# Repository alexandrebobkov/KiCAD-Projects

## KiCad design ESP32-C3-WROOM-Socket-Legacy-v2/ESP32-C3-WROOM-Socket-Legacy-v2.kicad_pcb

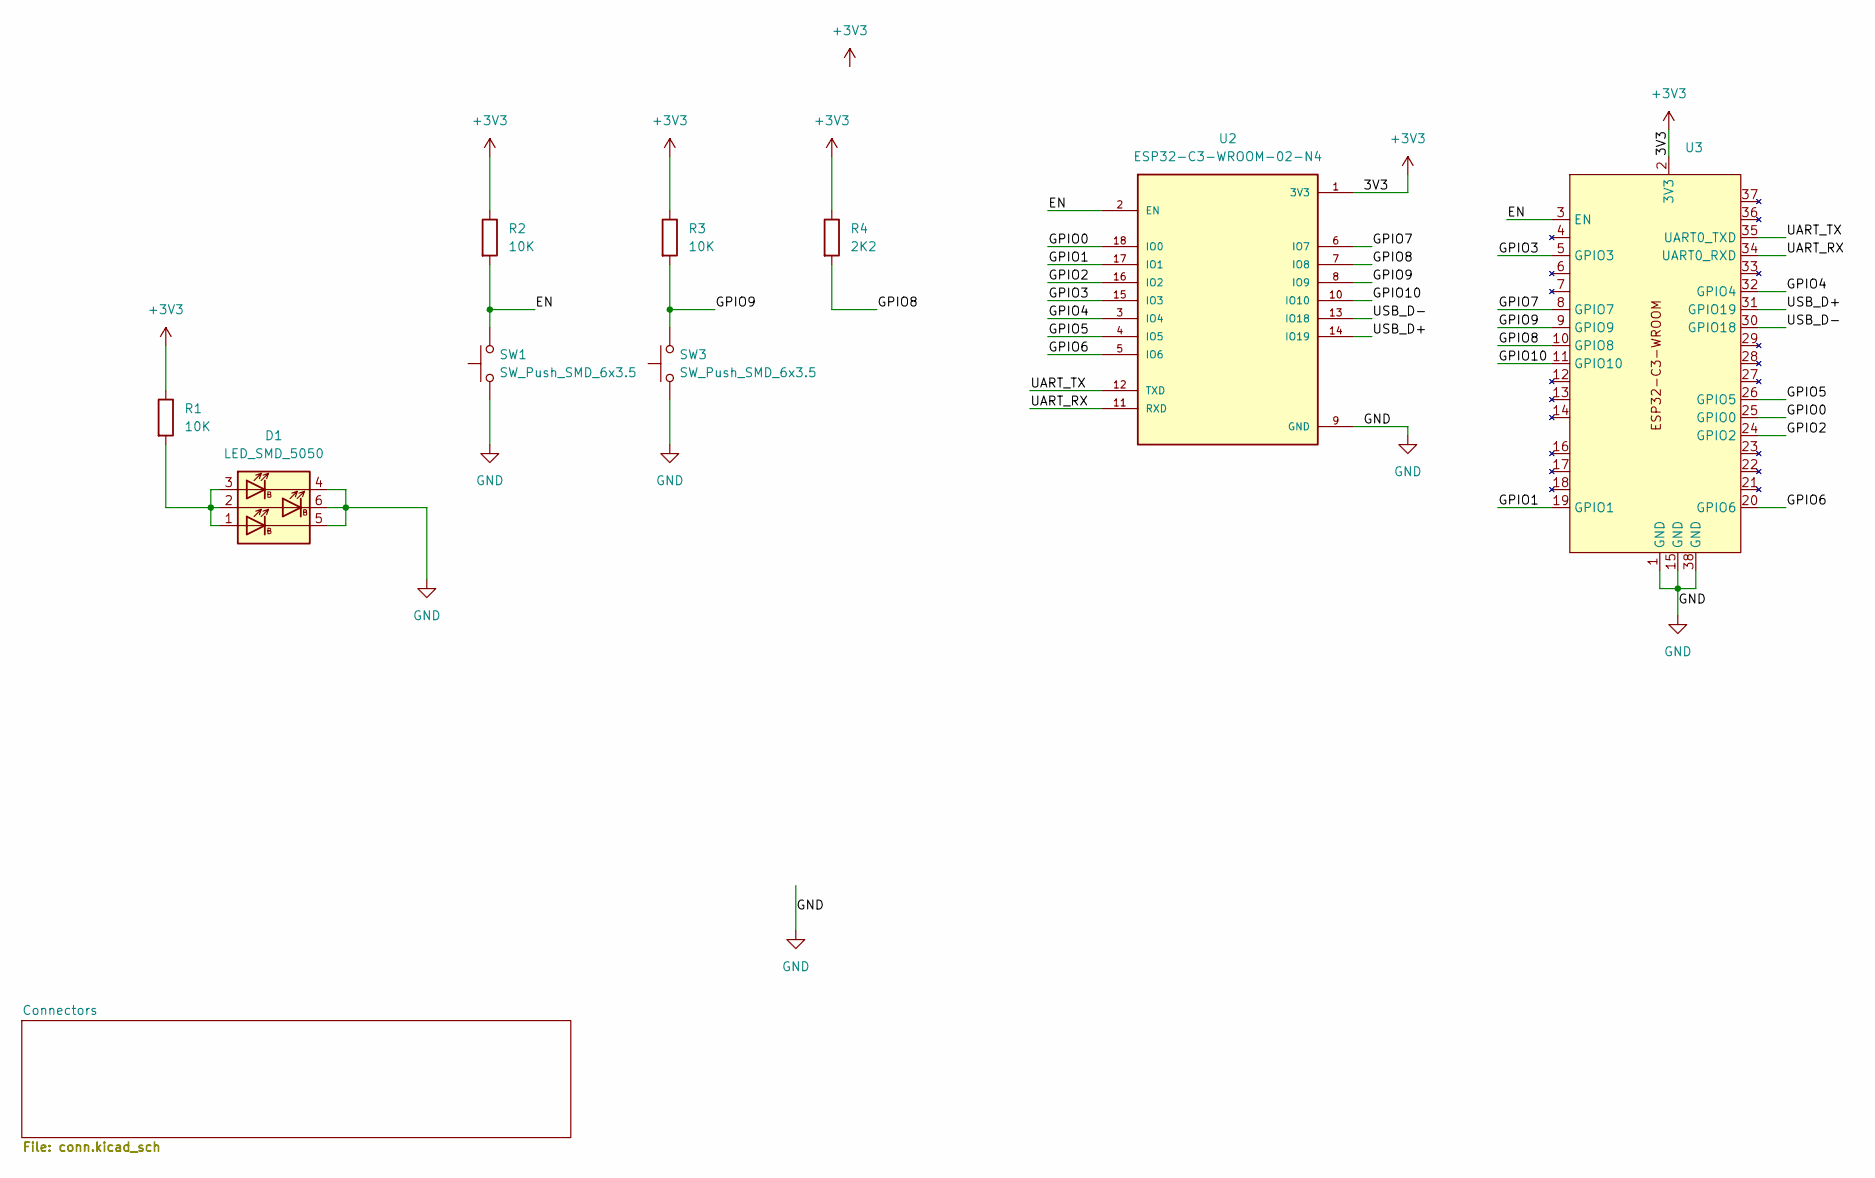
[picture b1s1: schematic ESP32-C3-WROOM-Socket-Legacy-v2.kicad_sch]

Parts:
D1: LED_SMD_5050; LED_5050-6
R1, R2, R3: 10K; R_1206_3216Metric_Pad1.30x1.75mm_HandSolder
R4: 2K2; R_1206_3216Metric_Pad1.30x1.75mm_HandSolder
SW1, SW3: SW_Push_SMD_6x3.5; SW_PUSH_6x3.5mm
U2: ESP32-C3-WROOM-02-N4; ESP32-C3-WROOM-02-H4
U3: CONN-ESP32-WROOM-Adapter-Legacy-v3

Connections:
+3V3: R1.1, R2.1, R3.1, R4.1, U2.1 (3V3), U3.2 (3V3)
/EN: R2.2, SW1.2, U2.2 (EN), U3.3 (EN)
/GPIO0: U2.18 (IO0), U3.25 (GPIO0)
/GPIO1: U2.17 (IO1), U3.19 (GPIO1)
/GPIO2: U2.16 (IO2), U3.24 (GPIO2)
/GPIO3: U2.15 (IO3), U3.5 (GPIO3)
/GPIO4: U2.3 (IO4), U3.32 (GPIO4)
/GPIO5: U2.4 (IO5), U3.26 (GPIO5)
/GPIO6: U2.5 (IO6), U3.20 (GPIO6)
/GPIO7: U2.6 (IO7), U3.8 (GPIO7)
/GPIO8: R4.2, U2.7 (IO8), U3.10 (GPIO8)
/GPIO9: R3.2, SW3.2, U2.8 (IO9), U3.9 (GPIO9)
/GPIO10: U2.10 (IO10), U3.11 (GPIO10)
/UART_RX: U2.11 (RXD), U3.34 (UART0_RXD)
/UART_TX: U2.12 (TXD), U3.35 (UART0_TXD)
/USB_D+: U2.14 (IO19), U3.31 (GPIO19)
/USB_D-: U2.13 (IO18), U3.30 (GPIO18)
GND: D1.4 (KR), D1.5 (AG), D1.6 (KR), SW1.1, SW3.1, U2.9 (GND), U2.19 (GND__1), U2.20 (GND__2), U2.21 (GND__3), U2.22 (GND__4), U2.23 (GND__5), U2.24 (GND__6), U2.25 (GND__7), U2.26 (GND__8), U2.27 (GND__9), U2.28 (GND__10), U2.29 (GND__11), U2.30 (GND__12), U2.31 (GND__13), U2.32 (GND__14), U2.33 (GND__15), U2.34 (GND__16), U2.35 (GND__17), U2.36 (GND__18), U2.37 (GND__19), U2.38 (GND__20), U2.39 (GND__21), U3.1 (GND), U3.15 (GND), U3.38 (GND)
unnamed: D1.1 (AB), D1.2 (KB), D1.3 (AR), R1.2

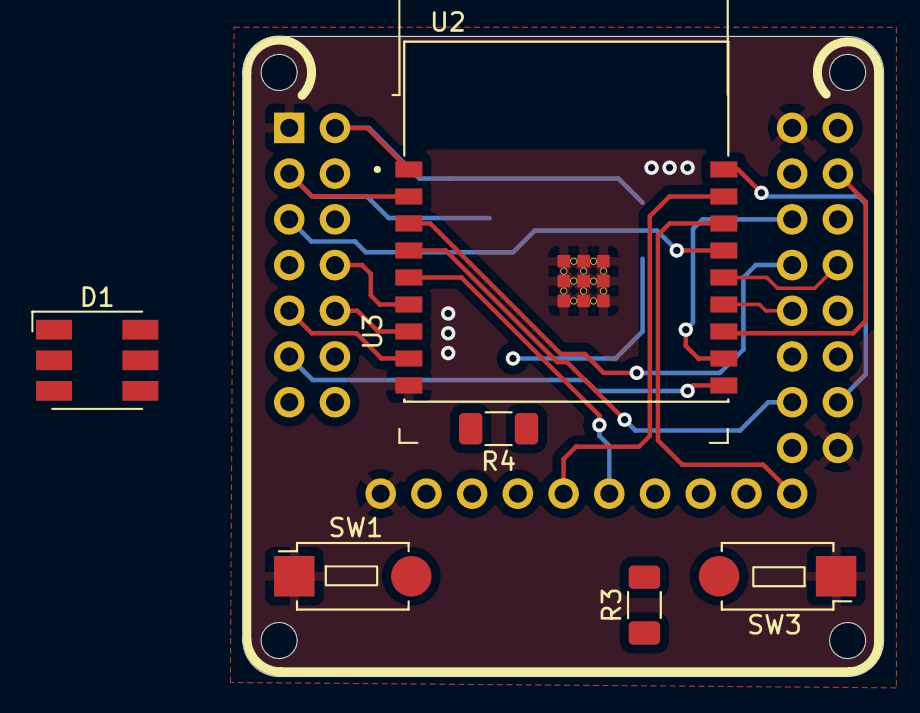
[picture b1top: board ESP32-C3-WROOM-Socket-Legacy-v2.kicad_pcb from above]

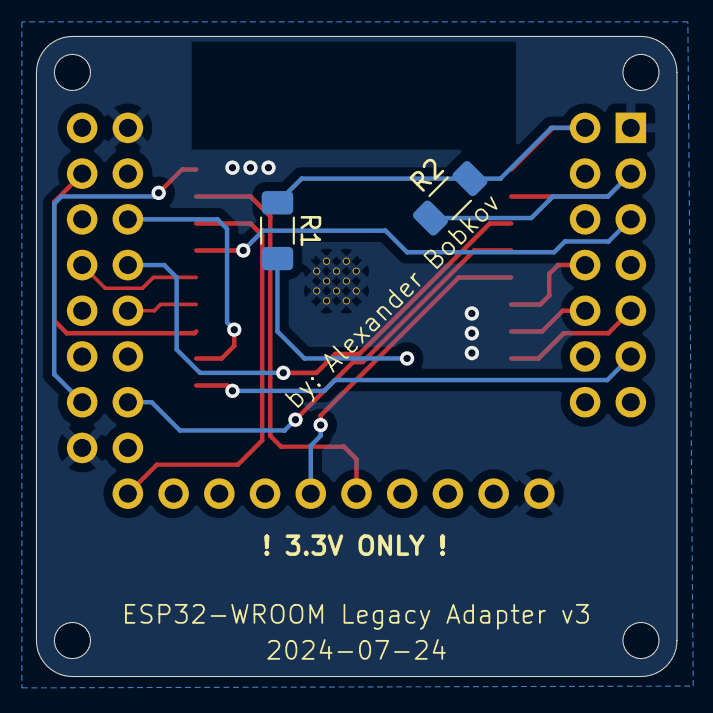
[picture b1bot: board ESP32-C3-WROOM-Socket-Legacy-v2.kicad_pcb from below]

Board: 2 copper layers, 35.6 x 35.6 mm, 9 parts (2 on the bottom side), 19 nets.

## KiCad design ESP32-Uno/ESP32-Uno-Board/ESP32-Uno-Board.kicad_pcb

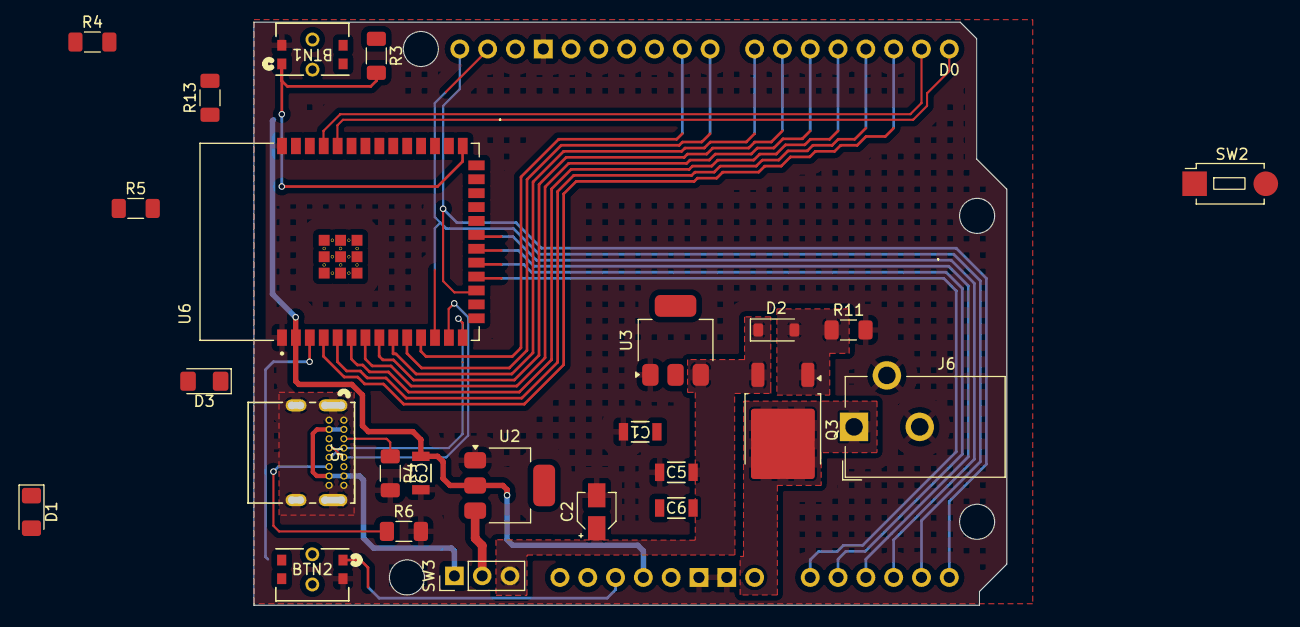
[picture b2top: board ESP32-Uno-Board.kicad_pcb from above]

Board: 2 copper layers, 68.8 x 53.2 mm, 27 parts (0 on the bottom side), 15 nets.

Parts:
A1: Arduino_Uno_WiFi_R2_Shield; Arduino Uno
BTN1, BTN2: SW_Push_SMD_6x3.5; Button-Tacktile-TL1014BF160
C1, C5, C9: 1uF; CAP_CL31_SAM
C2: 1000uF; CP_Elec_3x5.3
C6: 10uF; CAP_CL31_SAM
D1, D3: LED; LED_1206_3216Metric_Pad1.42x1.75mm_HandSolder
D2: MMSZ52XXB; D_SOD-123
H1: MountingHole; Arduino Uno
J5: USB-C_Receptacle_Data_16P_GCT-USB4085; USB-C_GCT CONN16_USB4085-GF-A
J6: Barrel_Jack_Switch; BarrelJack_CUI_PJ-102AH_Horizontal
Q3: DMP6180SK3; TO-252-2
R3, R4#2, R11, R13: 10k; R_1206_3216Metric_Pad1.30x1.75mm_HandSolder
R4, R6: 5K1; R_1206_3216Metric_Pad1.30x1.75mm_HandSolder
R5: 2K2; R_1206_3216Metric_Pad1.30x1.75mm_HandSolder
SW2: SW_Push_SMD_6x3.5; SW_PUSH_6x3.5mm
SW3: SW_SPDT; PinHeader_1x03_P2.54mm_Vertical
U2: LM1117MP-3.3; SOT-223
U3: AMS1117-5V; SOT-223
U6: ESP32-S3-WROOM-1; ESP32-S3-WROOM-2-N32R8V

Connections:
+3V3: A1.3V3 (3.3V), C9.1, D3.2 (A), R3.1, R4#2.1, R5.1, R13.1, U2.2 (VO), U6.2 (3V3)
+5V: A1.5V1 (5V), C1.1, U2.3 (VI), U3.2 (VO)
/CC1: J5.A5 (CC1), R4.1
/CC2: J5.B5 (CC2), R6.1
/G: D2.2 (A), Q3.1 (G), R11.1
/GPIO0: BTN1.1, R3.2, U6.27 (IO0)
/GPIO46: SW2.1, U6.16 (IO46)
/USB_D+: J5.A6 (D+), J5.B6 (D+), U6.14 (IO20)
/USB_D-: J5.A7 (D-), J5.B7 (D-), U6.13 (IO19)
/VIN: C2.1, C5.2, C6.1, D2.1 (K), Q3.3 (S), SW3.3 (C)
/VUSB: D1.2 (A), J5.A4 (VBUS), J5.A9 (VBUS), J5.B4 (VBUS), J5.B9 (VBUS), SW3.1 (A)
/~RESET: BTN2.1, R13.2, U6.3 (EN)
GND: A1.GND1 (GND), A1.GND2 (GND), A1.GND3 (GND), BTN1.2, BTN2.2, C1.2, C2.2, C5.1, C6.2, C9.2, J5.A1 (GND), J5.A12 (GND), J5.B1 (GND), J5.B12 (GND), J5.S1 (SHIELD), J5.S2 (SHIELD), J5.S3 (SHIELD), J5.S4 (SHIELD), J6.2, J6.3, R4.2, R6.2, R11.2, SW2.2, U2.1 (GND), U3.1 (ADJ), U6.1 (GND), U6.40 (GND)
PWR: J6.1, Q3.2 (D)
VCC: SW3.2 (B), U3.3 (VI)

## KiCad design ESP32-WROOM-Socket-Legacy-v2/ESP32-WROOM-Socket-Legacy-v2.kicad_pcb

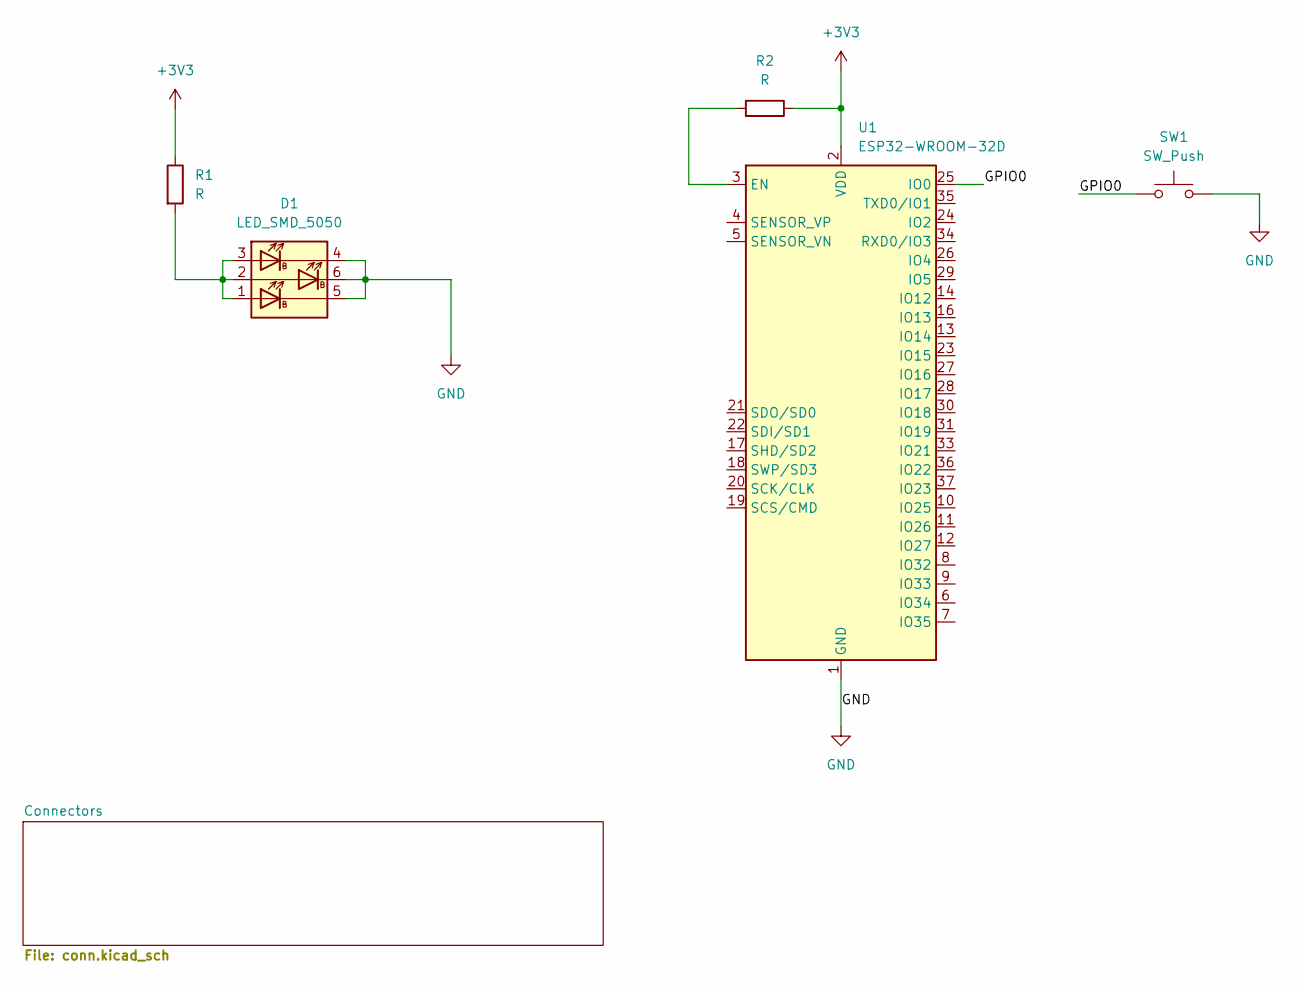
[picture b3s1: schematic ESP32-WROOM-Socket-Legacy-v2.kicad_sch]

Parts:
D1: LED_SMD_5050; LED_5050-6
R1, R2: R; R_1206_3216Metric_Pad1.30x1.75mm_HandSolder
SW1: SW_Push; SW_SPST_6x3
U1: ESP32-WROOM-32D; ESP32-WROOM-Adapter-Legacy-v3

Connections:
+3V3: R1.1, R2.1, U1.2 (VDD)
/GPIO0: SW1.1, U1.25 (IO0)
GND: D1.4 (KR), D1.5 (AG), D1.6 (KR), SW1.2, U1.1 (GND), U1.15 (GND), U1.38 (GND), U1.39 (GND)
unnamed: D1.1 (AB), D1.2 (KB), D1.3 (AR), R1.2
unnamed: R2.2, U1.3 (EN)

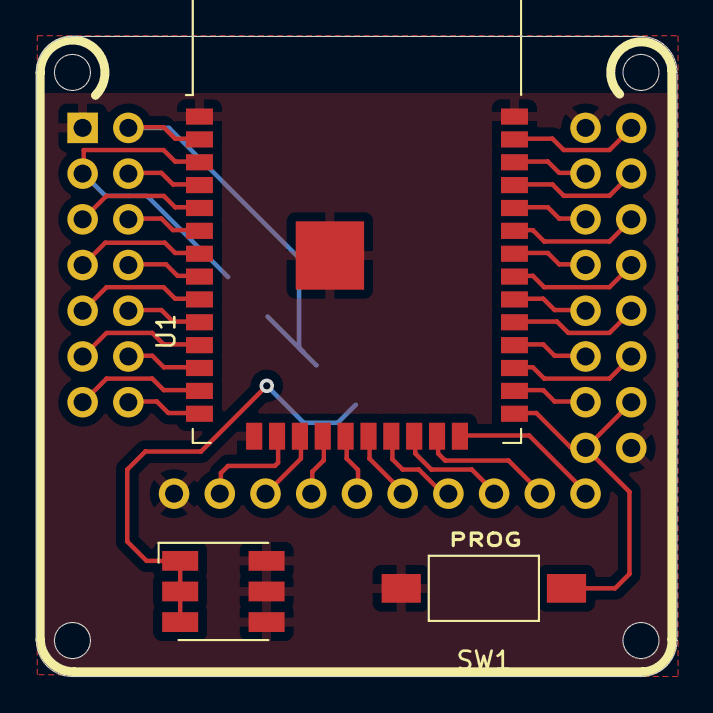
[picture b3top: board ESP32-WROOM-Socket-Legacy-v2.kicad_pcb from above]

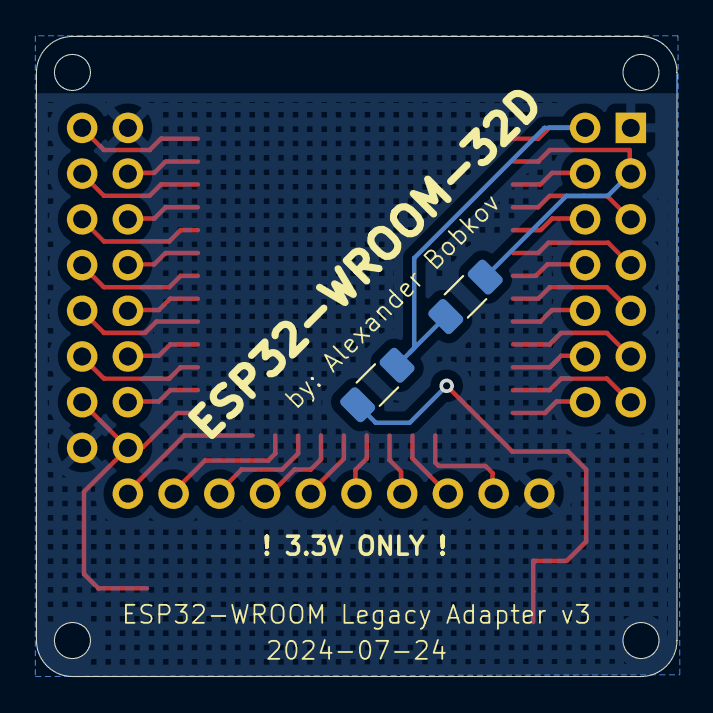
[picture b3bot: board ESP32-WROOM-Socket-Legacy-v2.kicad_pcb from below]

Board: 2 copper layers, 35.6 x 35.6 mm, 5 parts (2 on the bottom side), 5 nets.

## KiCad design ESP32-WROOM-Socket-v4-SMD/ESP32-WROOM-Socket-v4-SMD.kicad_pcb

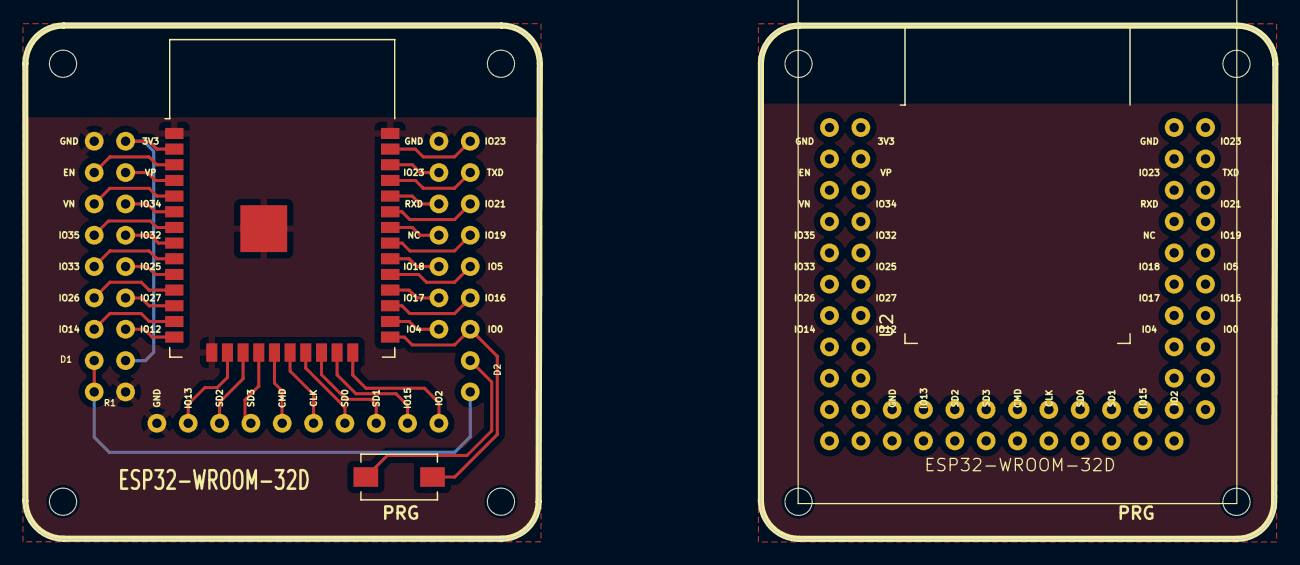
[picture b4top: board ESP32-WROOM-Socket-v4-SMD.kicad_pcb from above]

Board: 2 copper layers, 41.7 x 41.7 mm, 14 parts (0 on the bottom side), 6 nets.

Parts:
D1: PWR; LED_2.5mm
D2: PROG; LED_2.5mm
H1, H1#2, H2, H2#2, H3, H3#2, H4, H4#2: MountingHole_Pad_MP; MountingHole_2.2mm_M2
R1: R; R_2.5mm
SW1: PRG; SW_SPST_EVQPE1
U1: ESP32-WROOM-32D; ESP32-WROOM-Adapter-2
U2: ESP32-WROOM-32D; ESP32-WROOM-Adapter-Socket

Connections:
+3V3: D1.2 (A), U1.2 (VDD)
/PRG: SW1.1, U1.25 (IO0)
GND: R1.2, U1.1 (GND), U1.15 (GND), U1.38 (GND), U1.39 (GND)
unnamed: D1.1 (K), D2.1 (K), R1.1
unnamed: D2.2 (A), SW1.2
unnamed: U2.1 (GND), U2.38 (GND)

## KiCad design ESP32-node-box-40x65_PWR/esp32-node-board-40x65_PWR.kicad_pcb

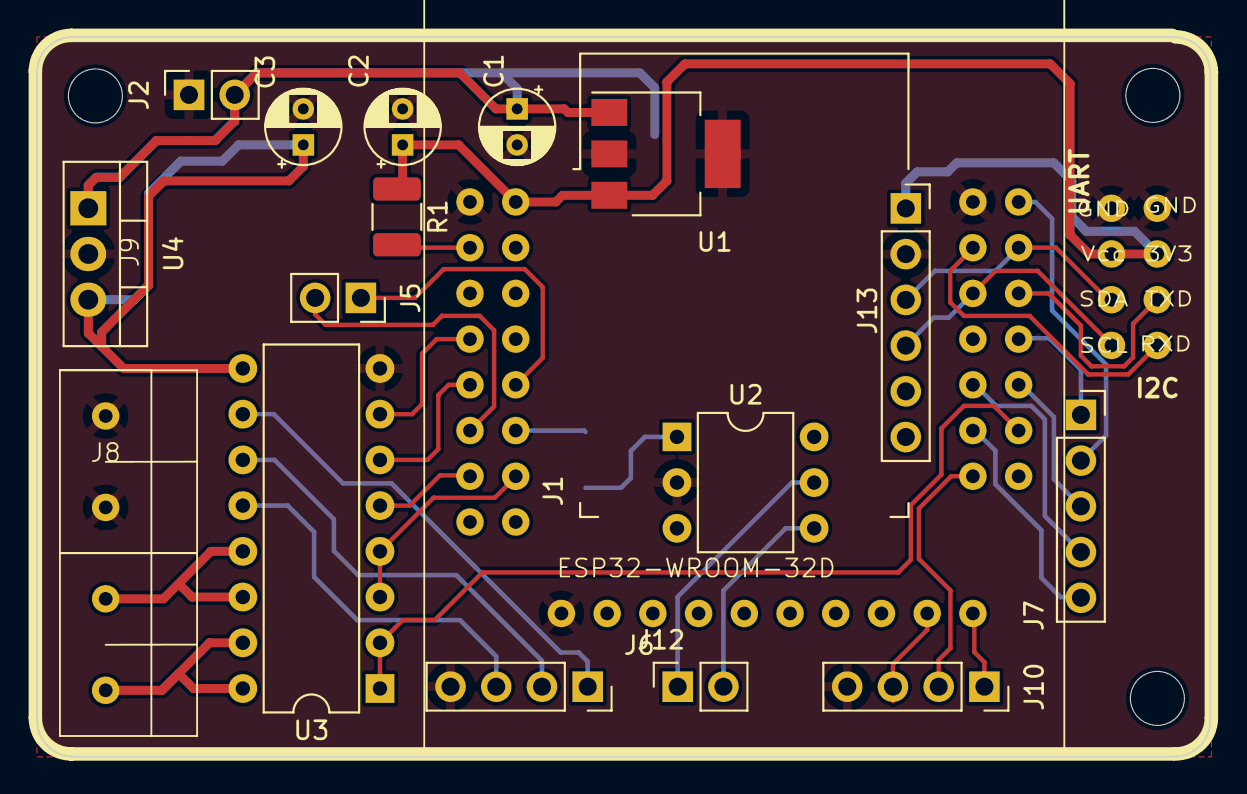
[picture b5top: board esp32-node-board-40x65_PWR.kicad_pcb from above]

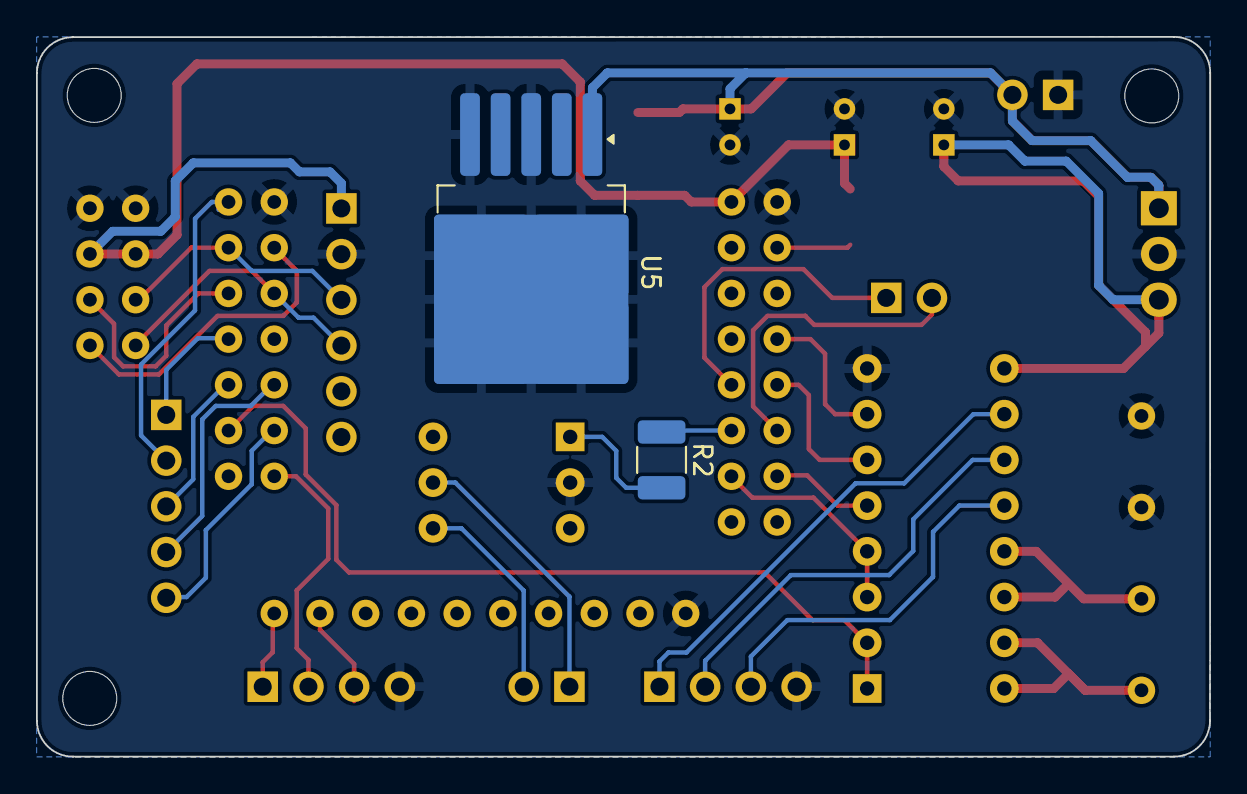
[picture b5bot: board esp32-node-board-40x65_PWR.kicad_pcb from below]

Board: 2 copper layers, 65.2 x 40.0 mm, 25 parts (2 on the bottom side), 33 nets.

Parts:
C1, C2, C3: 1uF; CP_Radial_D4.0mm_P2.00mm
H1, H2, H4: MountingHole_Pad; MountingHole_3mm
J1: ESP32-WROOM-Adapter-Socket-2
J2: PWD; PinSocket_1x02_P2.54mm_Vertical
J3: UART; Conn_UART
J4: I2C; Conn_I2C
J5: DAC_Socket; PinSocket_1x02_P2.54mm_Vertical
J6: SOURCE; PinSocket_1x04_P2.54mm_Vertical
J7: GPIO; PinSocket_1x05_P2.54mm_Vertical
J8, J9: Conn_01x02_Socket; Conn_Terminal_5mm
J10: ADC; PinSocket_1x04_P2.54mm_Vertical
J12: Conn_01x02_Socket; PinSocket_1x02_P2.54mm_Vertical
J13: Conn_01x06_Socket; PinSocket_1x06_P2.54mm_Vertical
R1: 10K; R_1210_3225Metric_Pad1.30x2.65mm_HandSolder
R2: 1K; R_1210_3225Metric_Pad1.30x2.65mm_HandSolder
U1: MAX1726EUK33; SOT-223-3_TabPin2
U2: 4N35; DIP-6_W7.62mm
U3: ULN2003; DIP-16_W7.62mm
U4: L7805; LD1117
U5: LM2596S-ADJ; TO-263-5_TabPin3

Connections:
+3V3: C2.1, J1.2 (VDD), J3.3V3, J4.Vcc (VCC), J13.1, R1.1, U1.3 (VO)
+5V: C3.1, U3.9 (COM), U4.3 (OUT)
/ADC2_CH0: J1.26 (IO4), J10.2
/ADC2_CH2: J1.24 (IO2), J10.1
/ADC2_CH3: J1.23 (IO15), J10.3
/DAC1: J1.10 (IO25), J5.1
/DAC2: J1.11 (IO26), J5.2
/EN: J1.3 (EN), R1.2
/GPIO5: J1.29 (IO5), J7.3
/GPIO17: J1.28 (IO17), J7.5
/GPIO18: J1.30 (IO18), J7.4
/GPIO19: J1.31 (IO19), J7.1
/GPIO23: J1.37 (IO23), J7.2
/GPIO27: J1.12 (IO27), R2.1
/OUT1: J1.27 (IO16), U3.1 (I1), U3.2 (I2)
/OUT2: J1.14 (IO12), U3.3 (I3), U3.4 (I4)
/OUT3: J1.13 (IO14), U3.5 (I5)
/OUT4: J1.9 (IO33), U3.6 (I6)
/OUT5: J1.7 (IO35), U3.7 (I7)
/RXD: J1.34 (RXD0), J3.RXD, J13.4
/SCL: J1.36 (SCL), J4.SCL
/SDA: J1.33 (SDA), J4.SDA
/SOURCE1: J8.2, U3.15 (O2), U3.16 (O1)
/SOURCE2: J8.1, U3.13 (O4), U3.14 (O3)
/SOURCE3: J6.3, U3.12 (O5)
/SOURCE4: J6.2, U3.11 (O6)
/SOURCE5: J6.1, U3.10 (O7)
/TXD: J1.35 (TXD0), J3.TXD, J13.3
/V1+: J12.1, U2.5
/V1-: J12.2, U2.4
/VDC: C1.1, J2.2, U1.1 (VI), U4.1 (IN), U5.1 (VIN)
GND: C1.2, C2.2, C3.2, J1.1 (GND), J1.15 (GND), J1.38 (GND), J2.1, J3.GND, J4.GND, J6.4, J9.1, J9.2, J10.4, J13.2, U1.2 (GND), U2.2, U3.8 (GND), U4.2 (GND), U5.3 (GND), U5.5 (~ON/OFF)
unnamed: R2.2, U2.1

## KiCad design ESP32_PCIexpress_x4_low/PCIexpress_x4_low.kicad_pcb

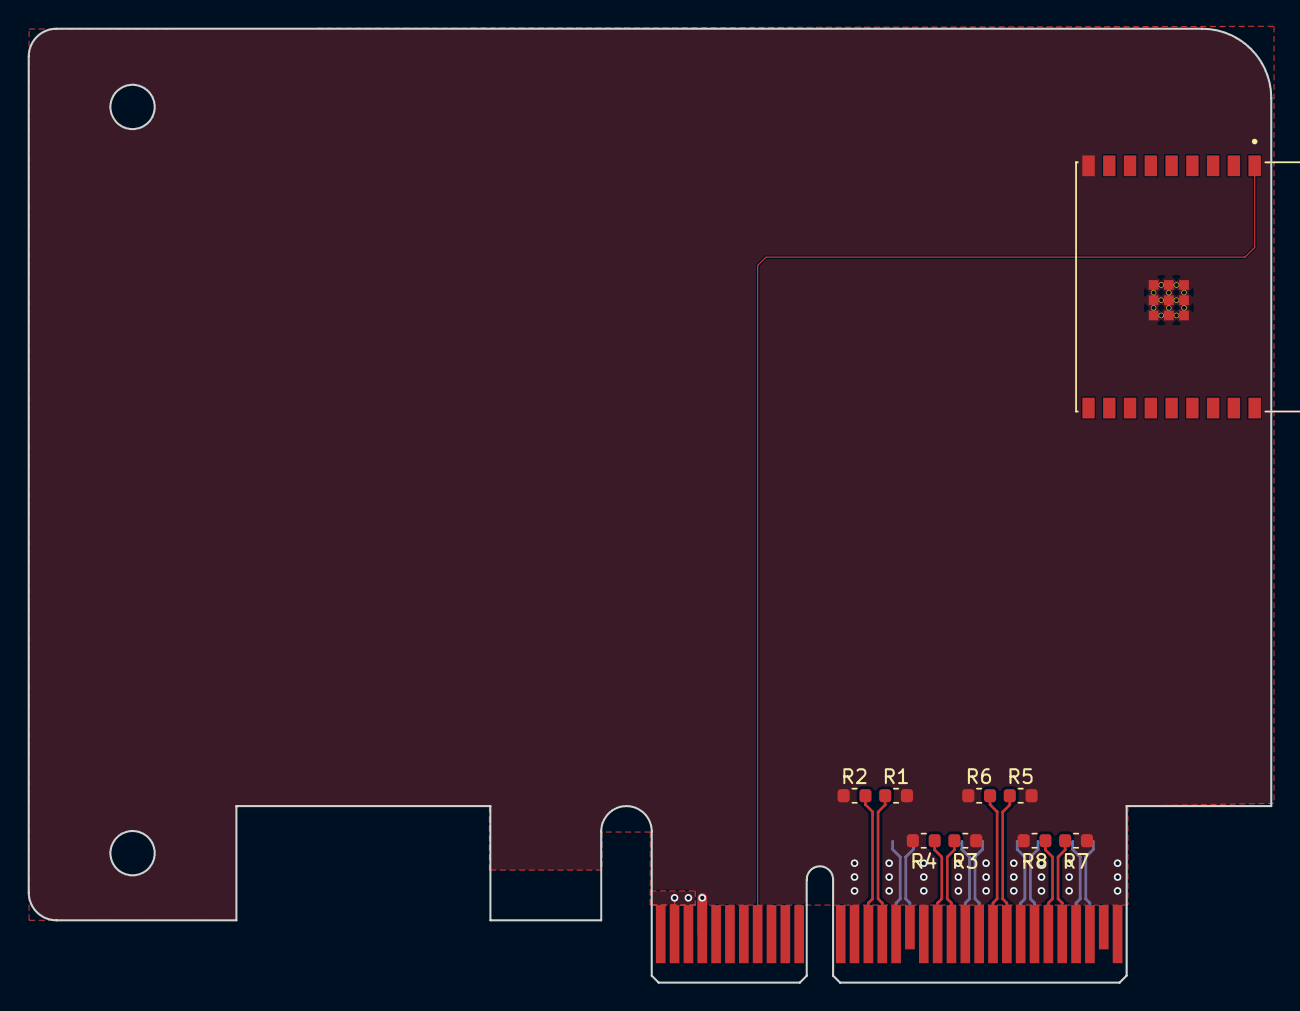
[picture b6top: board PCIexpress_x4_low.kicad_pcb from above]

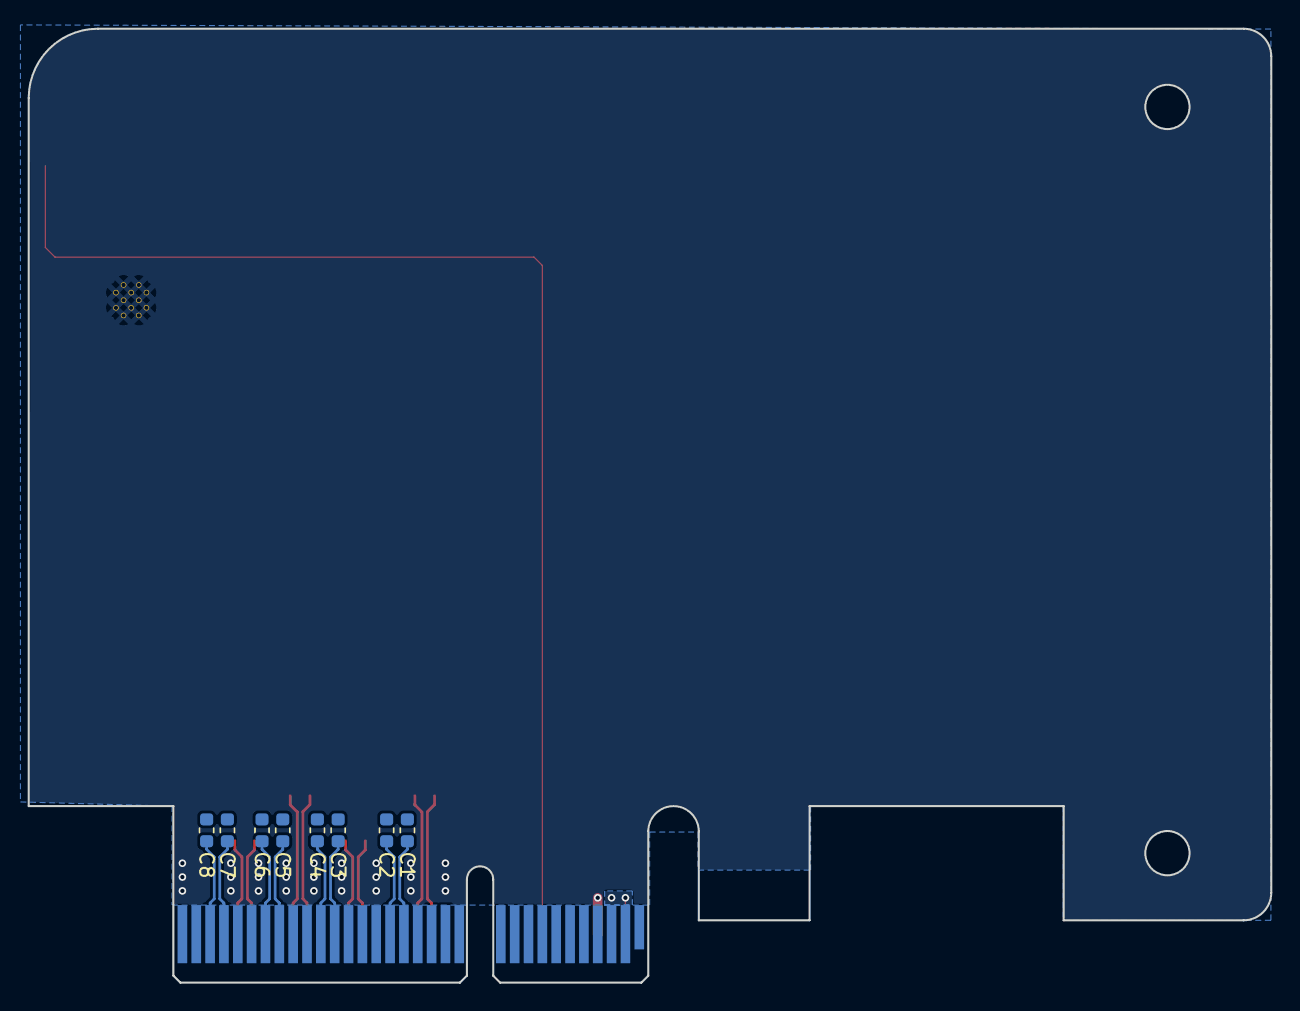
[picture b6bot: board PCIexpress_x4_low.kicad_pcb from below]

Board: 2 copper layers, 89.8 x 68.9 mm, 19 parts (8 on the bottom side), 19 nets.

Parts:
C1, C2, C3, C4, C5, C6, C7, C8: 100n; C_0603_1608Metric
J1: PCIexpress_bracket; PCIexpress_bracket_low
J2: PCIexpress_x4
R1, R2, R3, R4, R5, R6, R7, R8: 49.9; R_0603_1608Metric
U1: ESP32-C3-WROOM-02-N4; ESP32-C3-WROOM-02-H4

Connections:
+3V3: J2.A9 (+3.3V), J2.A10 (+3.3V), J2.B8 (+3.3V), U1.1 (3V3)
+12V: J2.A2 (+12V), J2.A3 (+12V), J2.B1 (+12V), J2.B2 (+12V), J2.B3 (+12V)
/PCIexpress_connector/_PER0_N: C2.1, J2.A17 (PERn0)
/PCIexpress_connector/_PER0_P: C1.2, J2.A16 (PERp0)
/PCIexpress_connector/_PER1_N: C4.1, J2.A22 (PERn1)
/PCIexpress_connector/_PER1_P: C3.2, J2.A21 (PERp1)
/PCIexpress_connector/_PER2_N: C6.1, J2.A26 (PERn2)
/PCIexpress_connector/_PER2_P: C5.2, J2.A25 (PERp2)
/PCIexpress_connector/_PER3_N: C8.1, J2.A30 (PERn3)
/PCIexpress_connector/_PER3_P: C7.2, J2.A29 (PERp3)
/PET0_N: J2.B15 (PETn0), R1.1
/PET0_P: J2.B14 (PETp0), R2.1
/PET1_N: J2.B20 (PETn1), R3.1
/PET1_P: J2.B19 (PETp1), R4.1
/PET2_N: J2.B24 (PETn2), R5.1
/PET2_P: J2.B23 (PETp2), R6.1
/PET3_N: J2.B28 (PETn3), R7.1
/PET3_P: J2.B27 (PETp3), R8.1
GND: J2.A4 (GND), J2.A12 (GND), J2.A15 (GND), J2.A18 (GND), J2.A20 (GND), J2.A23 (GND), J2.A24 (GND), J2.A27 (GND), J2.A28 (GND), J2.A31 (GND), J2.B4 (GND), J2.B7 (GND), J2.B13 (GND), J2.B16 (GND), J2.B18 (GND), J2.B21 (GND), J2.B22 (GND), J2.B25 (GND), J2.B26 (GND), J2.B29 (GND), J2.B32 (GND), R1.2, R2.2, R3.2, R4.2, R5.2, R6.2, R7.2, R8.2, U1.9 (GND__1), U1.19 (GND__1), U1.20 (GND__2), U1.21 (GND__3), U1.22 (GND__4), U1.23 (GND__5), U1.24 (GND__6), U1.25 (GND__7), U1.26 (GND__8), U1.27 (GND__9), U1.28 (GND__10), U1.29 (GND__11), U1.30 (GND__12), U1.31 (GND__13), U1.32 (GND__14), U1.33 (GND__15), U1.34 (GND__16), U1.35 (GND__17), U1.36 (GND__18), U1.37 (GND__19), U1.38 (GND__20), U1.39 (GND__21)

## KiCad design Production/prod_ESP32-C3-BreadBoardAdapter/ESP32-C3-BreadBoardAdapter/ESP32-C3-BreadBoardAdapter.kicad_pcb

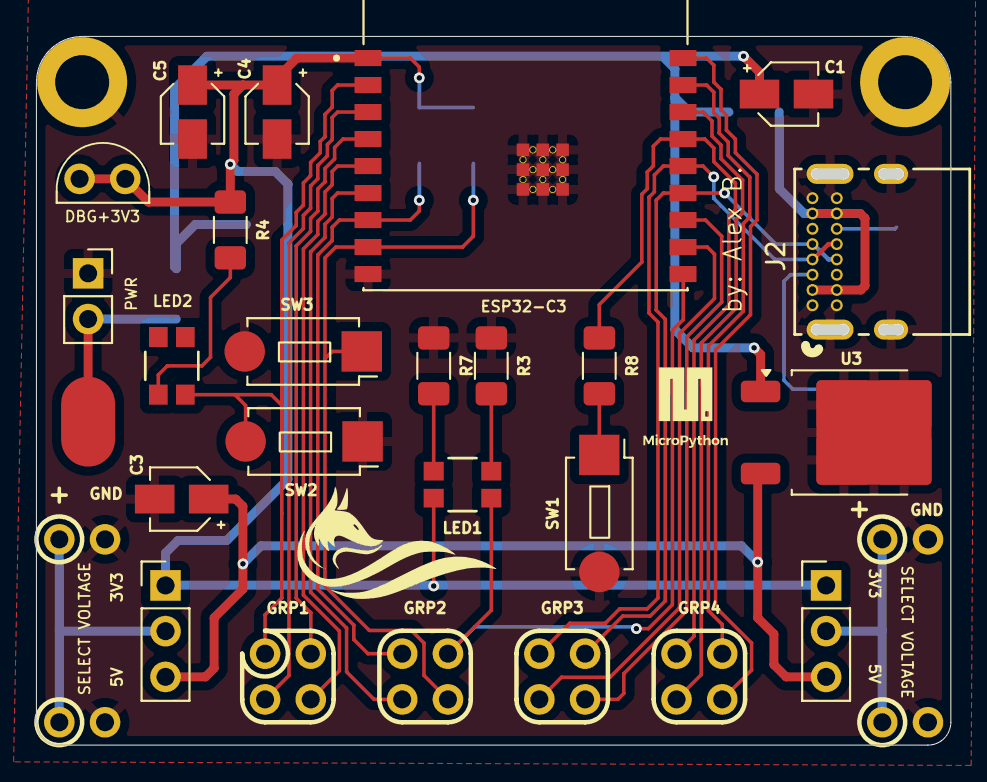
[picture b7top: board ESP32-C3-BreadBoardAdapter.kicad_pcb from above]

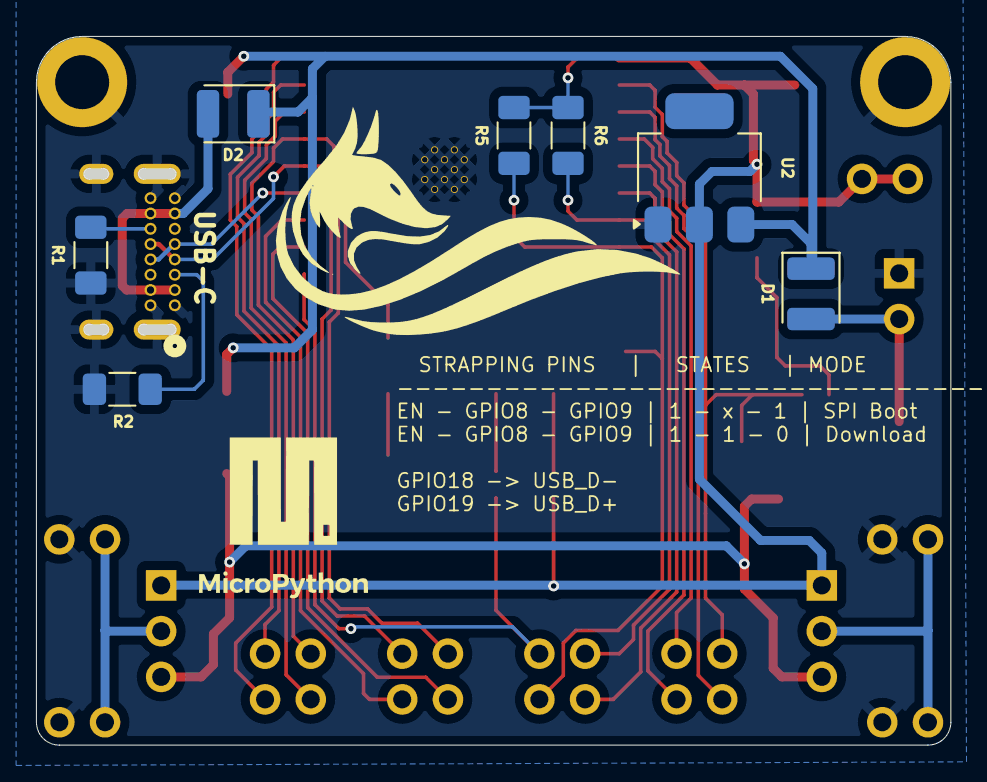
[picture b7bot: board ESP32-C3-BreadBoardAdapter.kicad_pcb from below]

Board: 2 copper layers, 50.8 x 39.4 mm, 29 parts (7 on the bottom side), 30 nets.

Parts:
C1, C3: 1uF; CP_Elec_3x5.3
C4: 10uF; CP_Elec_3x5.3
C5: 0.1uF; CP_Elec_3x5.3
D1, D2: D; D_1210_3225Metric
ESP32-C3: 16pins; BreadBoard-PowerAdapter-ESP32C3
J1: PWR; PinSocket_1x02_P2.54mm_Vertical
J2: USB-C_Receptacle_Data_16P_GCT-USB4085; USB-C_GCT CONN16_USB4085-GF-A
J3, J4: PWR_JMP; PinHeader_1x03_P2.54mm_Vertical
J6: Debug_3V3; Conn_Debug_1x02_P2.54mm
J7: Debug_VIN; Conn_Probe
LED1: LED-RED-GREEN-B1552USUG20D; LED_B1552_HVK-M
LED2: EN; LED_B1552_HVK-M
R1, R2, R3, R7: 5k1; R_1206_3216Metric_Pad1.30x1.75mm_HandSolder
R4: 10k; R_1206_3216Metric_Pad1.30x1.75mm_HandSolder
R5, R6, R8: 2K2; R_1206_3216Metric_Pad1.30x1.75mm_HandSolder
SW1, SW2, SW3: SW_Push_SMD_6x3.5; SW_PUSH_6x3.5mm
U1: ESP32-C3-WROOM-02-N4; ESP32-C3-WROOM-02-H4
U2: AMS1117-3V3; AMS1117 SOT-223
U3: L7805; TO-252-2

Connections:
3V3: C4.1, C5.1, J3.1, J4.1, J6.1 (DBG), LED1.2 (RED), R4.1, R5.1, R6.1, U1.1 (3V3), U2.2 (VO)
+5V: C3.1, J3.3, J4.3, U3.3 (OUT)
/IO0: ESP32-C3.16 (B8), U1.18 (IO0)
/IO1: ESP32-C3.15 (B7), U1.17 (IO1)
/IO2: ESP32-C3.14 (B6), U1.16 (IO2)
/IO3: ESP32-C3.13 (B5), R8.1, U1.15 (IO3)
/IO4: ESP32-C3.2 (A2), U1.3 (IO4)
/IO5: ESP32-C3.3 (A3), U1.4 (IO5)
/IO6: ESP32-C3.4 (A4), U1.5 (IO6)
/IO7: ESP32-C3.6 (A6), U1.6 (IO7)
/IO8: ESP32-C3.5 (A5), R6.2, U1.7 (IO8)
/IO9: ESP32-C3.8 (A8), R5.2, SW3.1, U1.8 (IO9)
/IO10: ESP32-C3.7 (A7), LED1.3 (GRN), U1.10 (IO10)
/RXD: ESP32-C3.10 (B2), U1.11 (RXD)
/TXD: ESP32-C3.12 (B4), U1.12 (TXD)
/VCC1: ESP32-C3.V1 (VCC1), J3.2
/VCC2: ESP32-C3.V2 (VCC2), J4.2
/VDC: D1.2 (A), J1.2, J7.1
EN: ESP32-C3.1 (A1), LED2.4 (GND), SW2.2, U1.2 (EN)
GND: C1.2, C3.2, C4.2, C5.2, ESP32-C3.G1 (GND1), ESP32-C3.G2 (GND2), ESP32-C3.GND, J1.1, J2.A1 (GND), J2.A12 (GND), J2.B1 (GND), J2.B12 (GND), J2.S1 (SHIELD), J2.S2 (SHIELD), J2.S3 (SHIELD), J2.S4 (SHIELD), R1.1, R2.1, R3.1, R7.1, SW1.2, SW2.1, SW3.2, U1.9 (GND), U1.19 (GND__1), U1.20 (GND__2), U1.21 (GND__3), U1.22 (GND__4), U1.23 (GND__5), U1.24 (GND__6), U1.25 (GND__7), U1.26 (GND__8), U1.27 (GND__9), U1.28 (GND__10), U1.29 (GND__11), U1.30 (GND__12), U1.31 (GND__13), U1.32 (GND__14), U1.33 (GND__15), U1.34 (GND__16), U1.35 (GND__17), U1.36 (GND__18), U1.37 (GND__19), U1.38 (GND__20), U1.39 (GND__21), U2.1 (ADJ), U3.2 (GND)
unnamed: D2.2 (A), J2.A4 (VBUS), J2.A9 (VBUS), J2.B4 (VBUS), J2.B9 (VBUS)
unnamed: J2.A5 (CC1), R2.2
unnamed: J2.B5 (CC2), R1.2
unnamed: LED1.1 (GND), R7.2
unnamed: LED1.4 (GND), R3.2
unnamed: LED2.3 (GRN), R4.2
unnamed: R8.2, SW1.1
USB_D+: ESP32-C3.9 (B1), J2.A6 (D+), J2.B6 (D+), U1.14 (IO19)
USB_D-: ESP32-C3.11 (B3), J2.A7 (D-), J2.B7 (D-), U1.13 (IO18)
VUSB: C1.1, D1.1 (K), D2.1 (K), U2.3 (VI), U3.1 (IN)
